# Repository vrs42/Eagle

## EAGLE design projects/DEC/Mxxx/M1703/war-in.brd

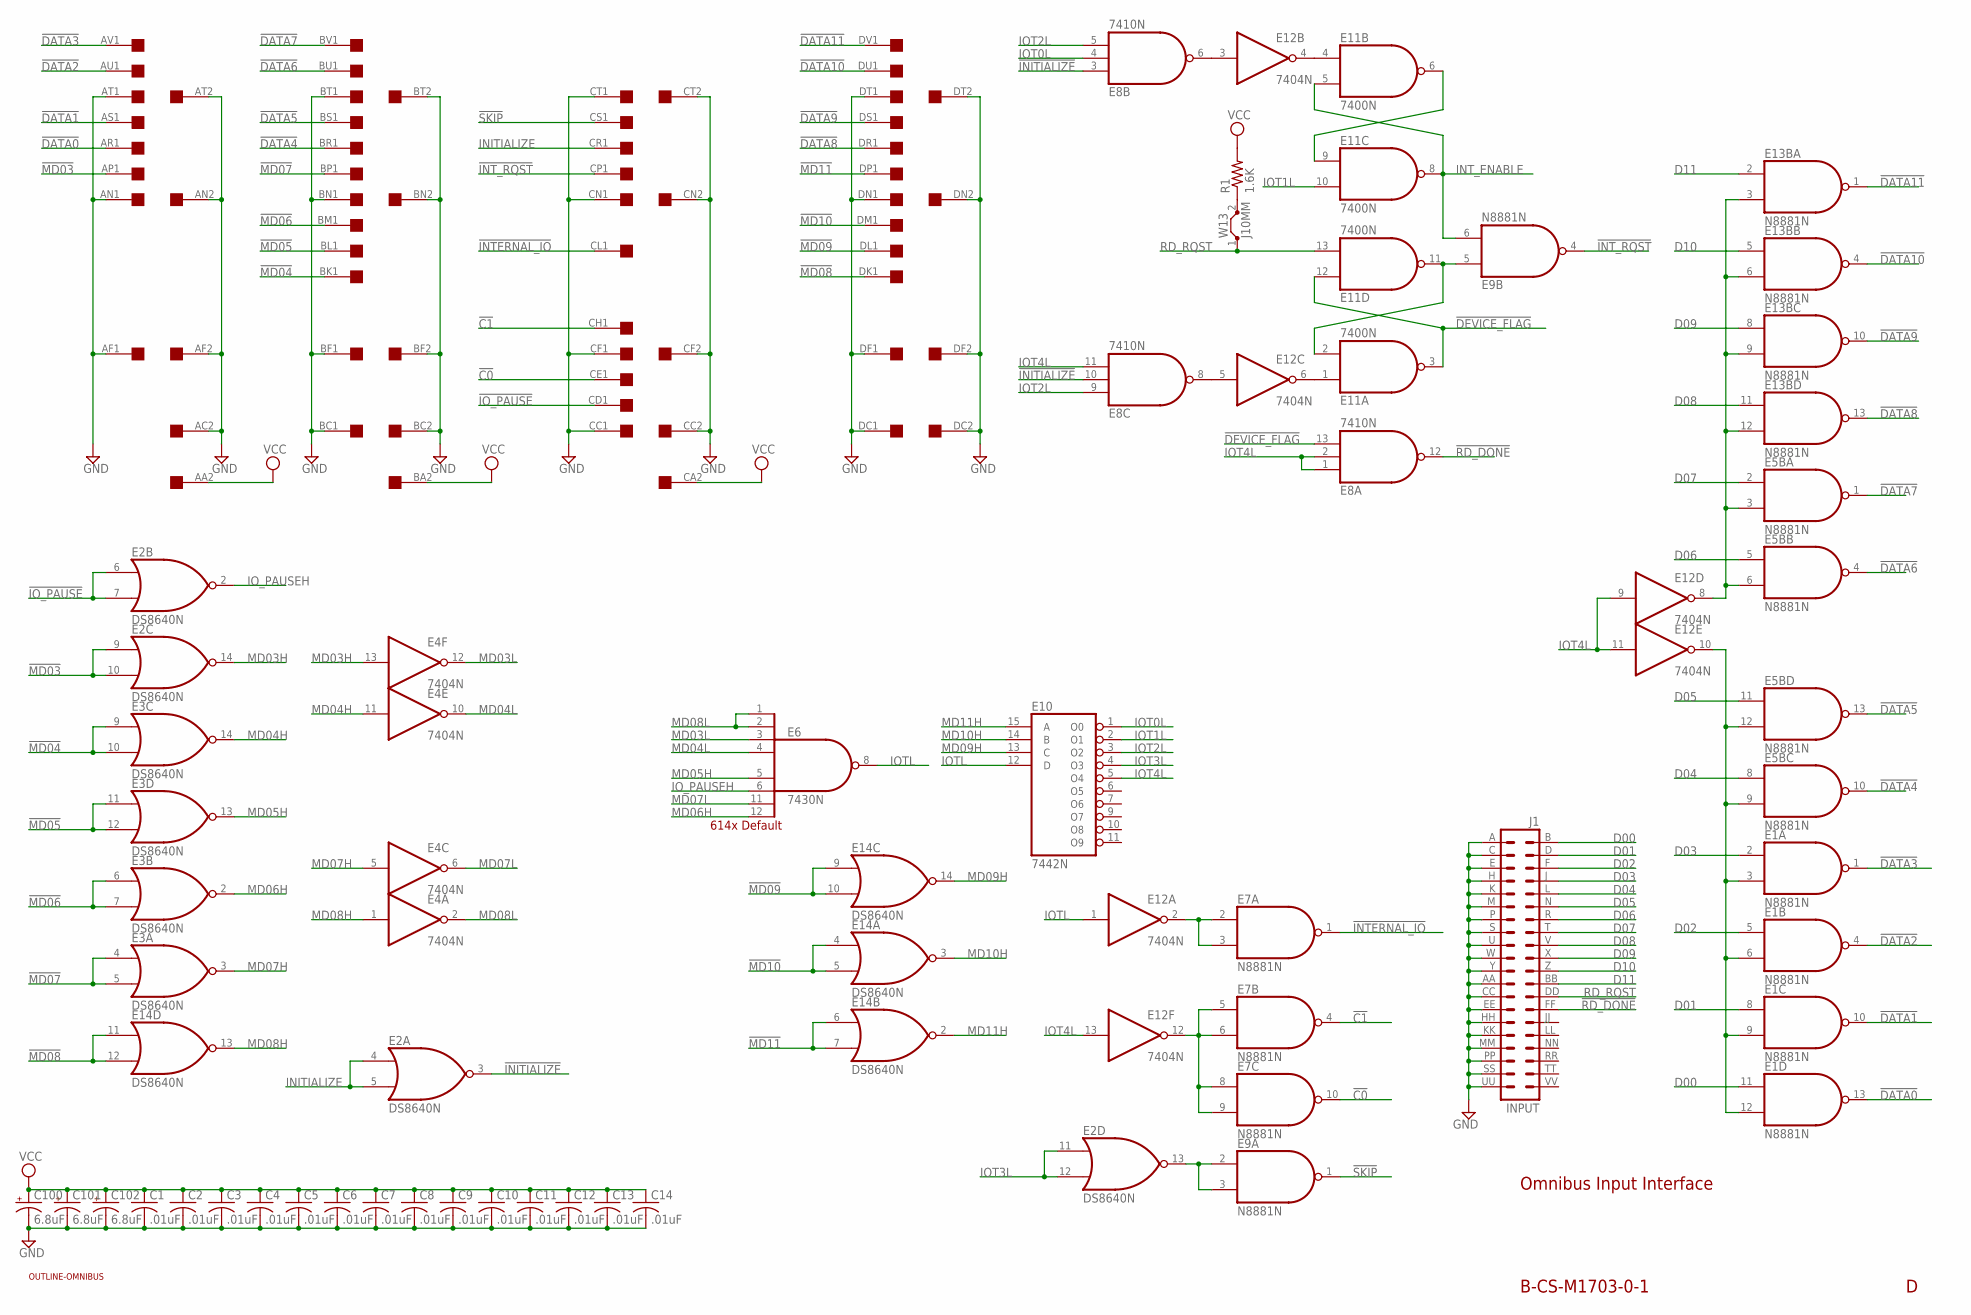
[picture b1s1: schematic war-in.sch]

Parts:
C1, C2, C3, C4, C5, C6, C7, C8, C9, C10, C11, C12, C13, C14: .01uF; C075-032X103
C100, C101, C102: 6.8uF; E12-8
E1, E5B, E7, E9, E13B: N8881N; DIL14
E2, E3, E14: DS8640N; DIL14
E4, E12: 7404N; DIL14
E6: 7430N; DIL14
E8: 7410N; DIL14
E10: 7442N; DIL16
E11: 7400N; DIL14
J1: INPUT; DEC40PINH
R1: 1.6K; 0207/10
U$2: QUAD; EDGE-CON8
U$4: OUTLINE-OMNIBUS; OMNIBUS
W13: J10MM; 10

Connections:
!C0: E7.10 (O), U$2.CE1
!C1: E7.4 (O), U$2.CH1
!DATA0: E1.13 (O), U$2.AR1
!DATA1: E1.10 (O), U$2.AS1
!DATA2: E1.4 (O), U$2.AU1
!DATA3: E1.1 (O), U$2.AV1
!DATA4: E5B.10 (O), U$2.BR1
!DATA5: E5B.13 (O), U$2.BS1
!DATA6: E5B.4 (O), U$2.BU1
!DATA7: E5B.1 (O), U$2.BV1
!DATA8: E13B.13 (O), U$2.DR1
!DATA9: E13B.10 (O), U$2.DS1
!DATA10: E13B.4 (O), U$2.DU1
!DATA11: E13B.1 (O), U$2.DV1
!DEVICE_FLAG: E8.13 (I2), E11.3 (O), E11.12 (I0)
!INITIALIZE: E2.3 (O), E8.3 (I0), E8.10 (I1)
!INTERNAL_IO: E7.1 (O), U$2.CL1
!INT_ENABLE: E11.6 (O), E11.9 (I0)
!INT_RQST: E9.4 (O), U$2.CP1
!IO_PAUSE: E2.6 (I0), E2.7 (I1), U$2.CD1
!MD03: E2.9 (I0), E2.10 (I1), U$2.AP1
!MD04: E3.9 (I0), E3.10 (I1), U$2.BK1
!MD05: E3.11 (I0), E3.12 (I1), U$2.BL1
!MD06: E3.6 (I0), E3.7 (I1), U$2.BM1
!MD07: E3.4 (I0), E3.5 (I1), U$2.BP1
!MD08: E14.11 (I0), E14.12 (I1), U$2.DK1
!MD09: E14.9 (I0), E14.10 (I1), U$2.DL1
!MD10: E14.4 (I0), E14.5 (I1), U$2.DM1
!MD11: E14.6 (I0), E14.7 (I1), U$2.DP1
!RD_DONE: E8.12 (O), J1.FF (28)
!SKIP: E9.1 (O), U$2.CS1
D00: E1.11 (I0), J1.B (2)
D01: E1.8 (I0), J1.D (4)
D02: E1.5 (I0), J1.F (6)
D03: E1.2 (I0), J1.J (8)
D04: E5B.8 (I0), J1.L (10)
D05: E5B.11 (I0), J1.N (12)
D06: E5B.5 (I0), J1.R (14)
D07: E5B.2 (I0), J1.T (16)
D08: E13B.11 (I0), J1.V (18)
D09: E13B.8 (I0), J1.X (20)
D10: E13B.5 (I0), J1.Z (22)
D11: E13B.2 (I0), J1.BB (24)
DEVICE_FLAG: E9.5 (I0), E11.2 (I1), E11.11 (O)
GND: C1.2, C2.2, C3.2, C4.2, C5.2, C6.2, C7.2, C8.2, C9.2, C10.2, C11.2, C12.2, C13.2, C14.2, C100.-, C101.-, C102.-, E1.7 (GND), E2.1 (GND), E3.1 (GND), E4.7 (GND), E5B.7 (GND), E6.7 (GND), E7.7 (GND), E8.7 (GND), E9.7 (GND), E10.8 (GND), E11.7 (GND), E12.7 (GND), E13B.7 (GND), E14.1 (GND), J1.A (1), J1.AA (23), J1.C (3), J1.CC (25), J1.E (5), J1.EE (27), J1.H (7), J1.HH (29), J1.K (9), J1.KK (31), J1.M (11), J1.MM (33), J1.P (13), J1.PP (35), J1.S (15), J1.SS (37), J1.U (17), J1.UU (39), J1.W (19), J1.Y (21), U$2.AC2, U$2.AF1, U$2.AF2, U$2.AN1, U$2.AN2, U$2.AT1, U$2.AT2, U$2.BC1, U$2.BC2, U$2.BF1, U$2.BF2, U$2.BN1, U$2.BN2, U$2.BT1, U$2.BT2, U$2.CC1, U$2.CC2, U$2.CF1, U$2.CF2, U$2.CN1, U$2.CN2, U$2.CT1, U$2.CT2, U$2.DC1, U$2.DC2, U$2.DF1, U$2.DF2, U$2.DN1, U$2.DN2, U$2.DT1, U$2.DT2
INITIALIZE: E2.4 (I0), E2.5 (I1), U$2.CR1
INT_ENABLE: E9.6 (I1), E11.5 (I1), E11.8 (O)
IOT0L: E8.4 (I1), E10.1 (O0)
IOT1L: E10.2 (O1), E11.10 (I1)
IOT2L: E8.5 (I2), E8.9 (I0), E10.3 (O2)
IOT3L: E2.11 (I0), E2.12 (I1), E10.4 (O3)
IOT4L: E8.1 (I0), E8.2 (I1), E8.11 (I2), E10.5 (O4), E12.9 (I), E12.11 (I), E12.13 (I)
IOTL: E6.8 (O), E10.12 (D), E12.1 (I)
IO_PAUSEH: E2.2 (O), E6.6 (I5)
MD03H: E2.14 (O), E4.13 (I)
MD03L: E4.12 (O), E6.3 (I2)
MD04H: E3.14 (O), E4.11 (I)
MD04L: E4.10 (O), E6.4 (I3)
MD05H: E3.13 (O), E6.5 (I4)
MD06H: E3.2 (O), E6.12 (I7)
MD07H: E3.3 (O), E4.5 (I)
MD07L: E4.6 (O), E6.11 (I6)
MD08H: E4.1 (I), E14.13 (O)
MD08L: E4.2 (O), E6.1 (I0), E6.2 (I1)
MD09H: E10.13 (C), E14.14 (O)
MD10H: E10.14 (B), E14.3 (O)
MD11H: E10.15 (A), E14.2 (O)
unnamed: E1.3 (I1), E1.6 (I1), E1.9 (I1), E1.12 (I1), E5B.9 (I1), E5B.12 (I1), E12.10 (O)
unnamed: R1.1, W13.2
unnamed: E5B.3 (I1), E5B.6 (I1), E12.8 (O), E13B.3 (I1), E13B.6 (I1), E13B.9 (I1), E13B.12 (I1)
unnamed: E11.4 (I0), E12.4 (O)
unnamed: E2.13 (O), E9.2 (I0), E9.3 (I1)
unnamed: E8.6 (O), E12.3 (I)
unnamed: E11.1 (I0), E12.6 (O)
unnamed: E8.8 (O), E12.5 (I)
unnamed: E7.2 (I0), E7.3 (I1), E12.2 (O)
unnamed: E7.5 (I0), E7.6 (I1), E7.8 (I0), E7.9 (I1), E12.12 (O)
RD_RQST: E11.13 (I1), J1.DD (26), W13.1
VCC: C1.1, C2.1, C3.1, C4.1, C5.1, C6.1, C7.1, C8.1, C9.1, C10.1, C11.1, C12.1, C13.1, C14.1, C100.+, C101.+, C102.+, E1.14 (VCC), E2.8 (VCC), E3.8 (VCC), E4.14 (VCC), E5B.14 (VCC), E6.14 (VCC), E7.14 (VCC), E8.14 (VCC), E9.14 (VCC), E10.16 (VCC), E11.14 (VCC), E12.14 (VCC), E13B.14 (VCC), E14.8 (VCC), R1.2, U$2.AA2, U$2.BA2, U$2.CA2

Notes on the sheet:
B-CS-M1703-0-1
Omnibus Input Interface
614x Default

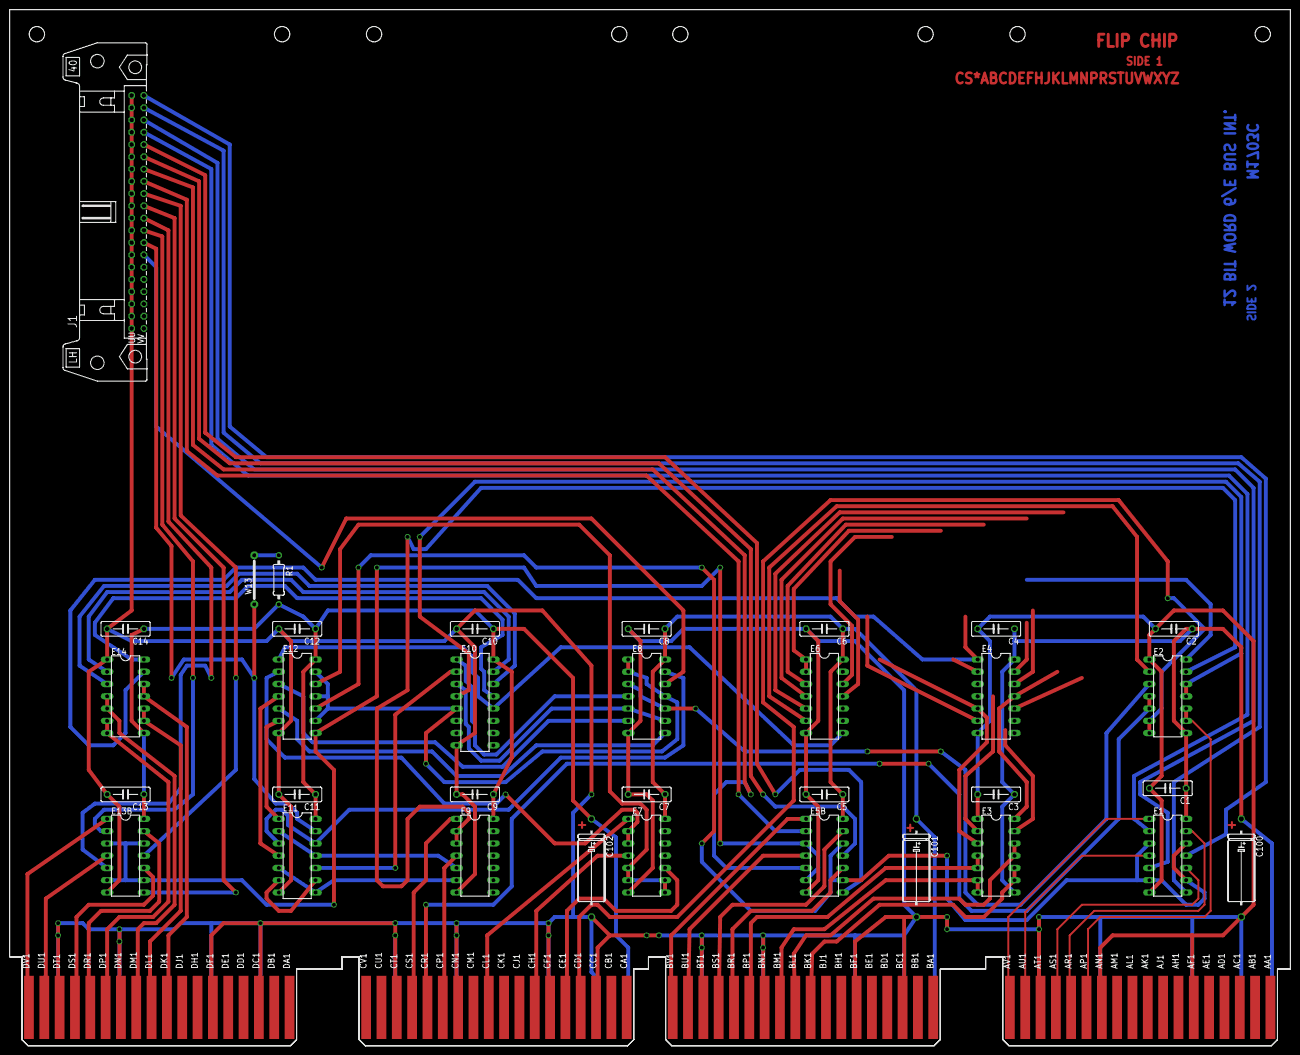
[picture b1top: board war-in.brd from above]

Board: 2 copper layers, 265.3 x 214.6 mm, 37 parts (0 on the bottom side), 79 nets.

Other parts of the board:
U$3: FLIPCHIP

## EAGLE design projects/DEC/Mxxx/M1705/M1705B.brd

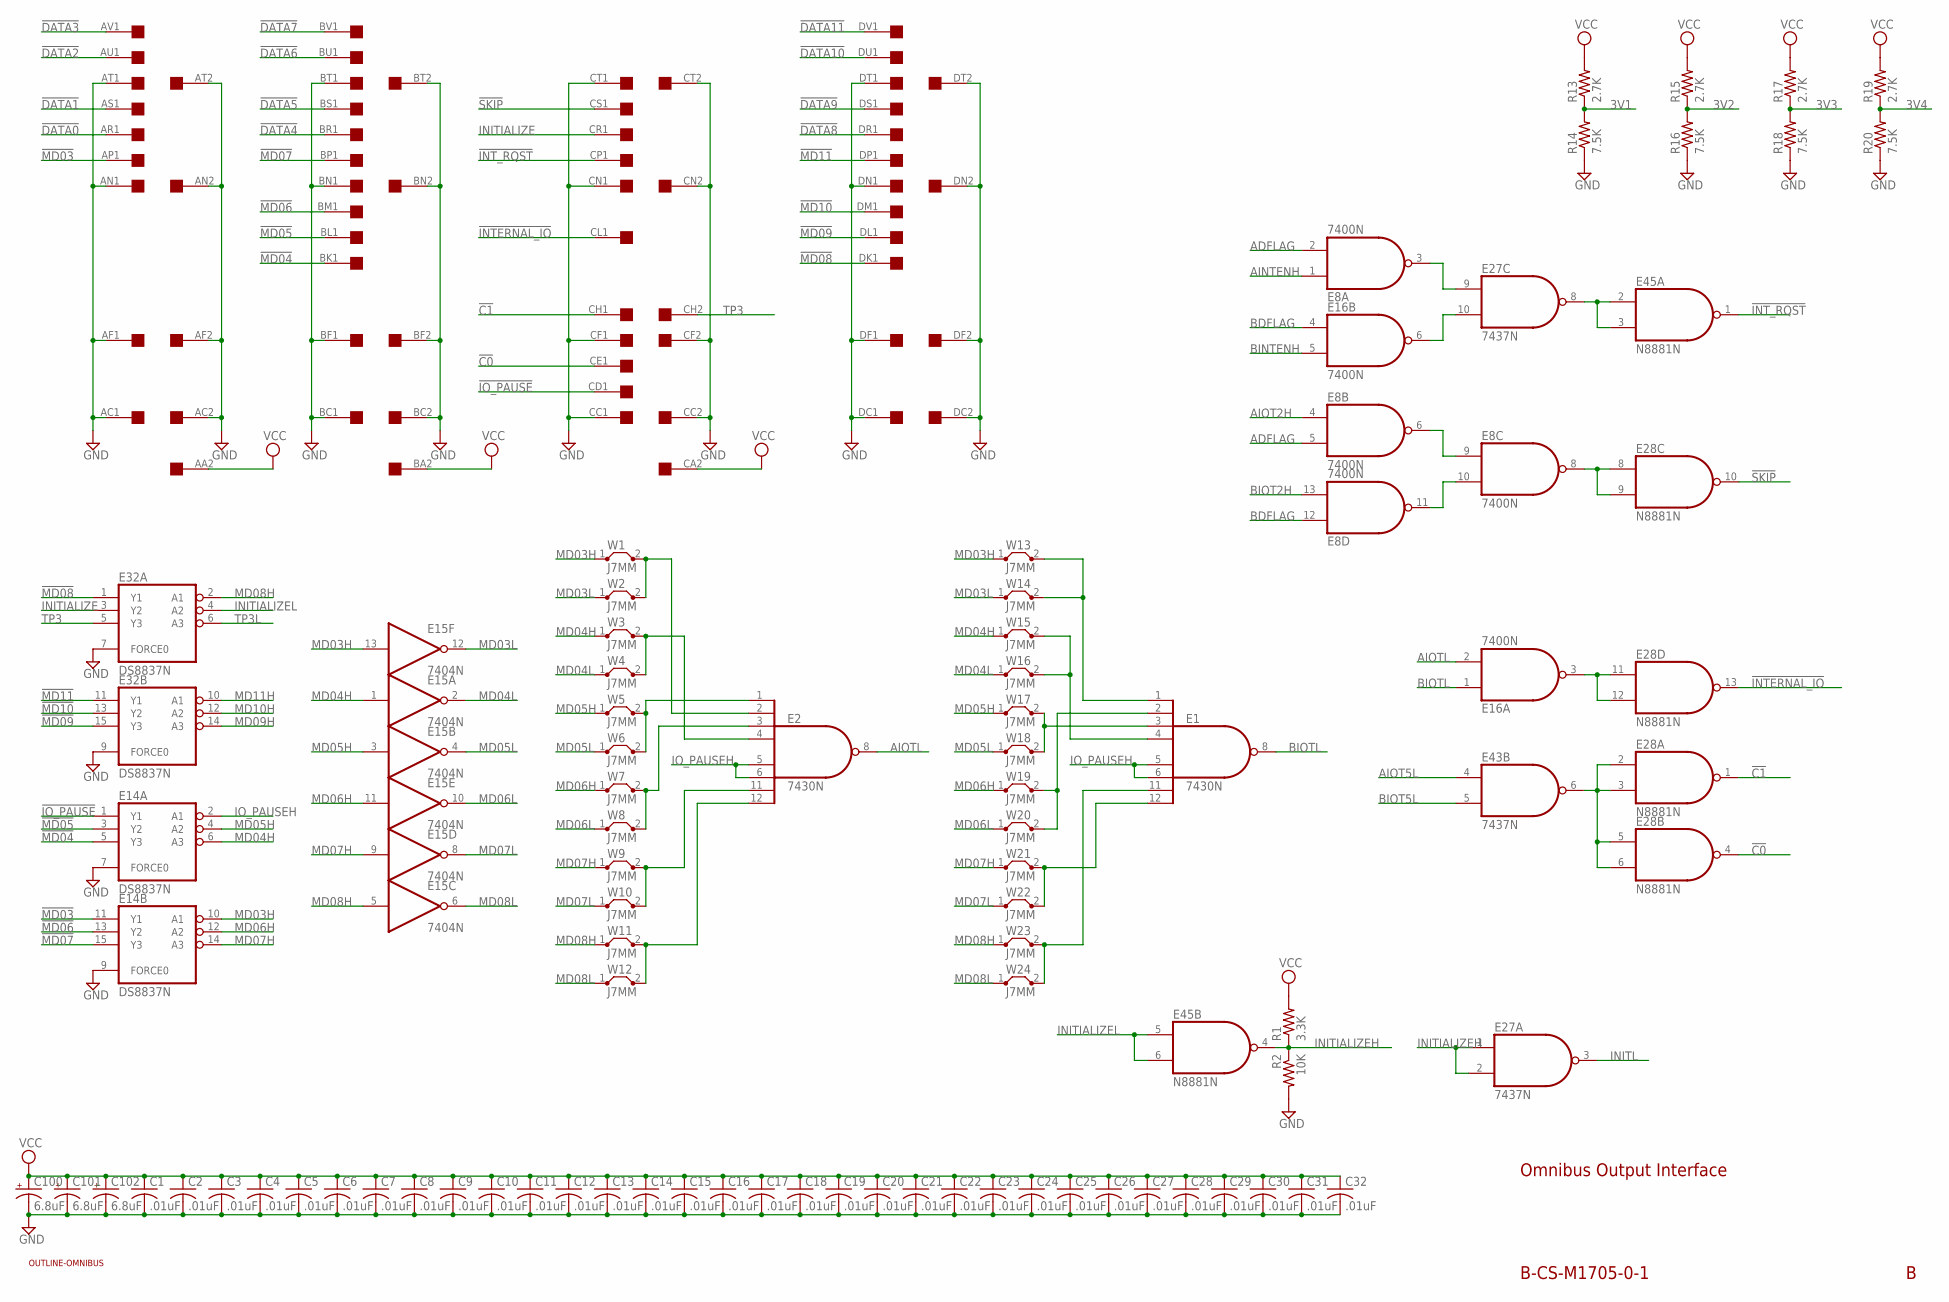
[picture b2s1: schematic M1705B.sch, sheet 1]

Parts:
C1, C2, C3, C4, C5, C6, C7, C8, C9, C10, C11, C12, C13, C14, C15, C16, C17, C18, C19, C20, C21, C22, C23, C24, C25, C26, C27, C28, C29, C30, C31, C32: .01uF; C075-032X103
C100, C101, C102: 6.8uF; E12-8
E1, E2: 7430N; DIL14
E8, E16: 7400N; DIL14
E14, E32: DS8837N; DIL16
E15: 7404N; DIL14
E27, E43: 7437N; DIL14
E28, E45: N8881N; DIL14
R1: 3.3K; 0207/10
R2: 10K; 0207/10
R13, R15, R17, R19: 2.7K; 0207/10
R14, R16, R18, R20: 7.5K; 0207/10
U$2: QUAD; EDGE-CON8
U$4: OUTLINE-OMNIBUS; OMNIBUS
W1, W2, W3, W4, W5, W6, W7, W8, W9, W10, W11, W12, W13, W14, W15, W16, W17, W18, W19, W20, W21, W22, W23, W24: J7MM; 07

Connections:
3V1: R13.1, R14.2; also elsewhere on the board
3V2: R15.1, R16.2; also elsewhere on the board
3V3: R17.1, R18.2; also elsewhere on the board
3V4: R19.1, R20.2; also elsewhere on the board
!C0: E28.4 (O), U$2.CE1
!C1: E28.1 (O), U$2.CH1
!DATA0: U$2.AR1; also elsewhere on the board
!DATA1: U$2.AS1; also elsewhere on the board
!DATA2: U$2.AU1; also elsewhere on the board
!DATA3: U$2.AV1; also elsewhere on the board
!DATA4: U$2.BR1; also elsewhere on the board
!DATA5: U$2.BS1; also elsewhere on the board
!DATA6: U$2.BU1; also elsewhere on the board
!DATA7: U$2.BV1; also elsewhere on the board
!DATA8: U$2.DR1; also elsewhere on the board
!DATA9: U$2.DS1; also elsewhere on the board
!DATA10: U$2.DU1; also elsewhere on the board
!DATA11: U$2.DV1; also elsewhere on the board
!INTERNAL_IO: E28.13 (O), U$2.CL1
!INT_RQST: E45.1 (O), U$2.CP1
!IO_PAUSE: E14.1 (Y1), U$2.CD1
!MD03: E14.11 (Y1), U$2.AP1
!MD04: E14.5 (Y3), U$2.BK1
!MD05: E14.3 (Y2), U$2.BL1
!MD06: E14.13 (Y2), U$2.BM1
!MD07: E14.15 (Y3), U$2.BP1
!MD08: E32.1 (Y1), U$2.DK1
!MD09: E32.15 (Y3), U$2.DL1
!MD10: E32.13 (Y2), U$2.DM1
!MD11: E32.11 (Y1), U$2.DP1
!SKIP: E28.10 (O), U$2.CS1
ADFLAG: E8.2 (I1), E8.5 (I1); also elsewhere on the board
AINTENH: E8.1 (I0); also elsewhere on the board
AIOT2H: E8.4 (I0); also elsewhere on the board
AIOT5L: E43.4 (I0); also elsewhere on the board
AIOTL: E2.8 (O), E16.2 (I1); also elsewhere on the board
BDFLAG: E8.12 (I0), E16.4 (I0); also elsewhere on the board
BINTENH: E16.5 (I1); also elsewhere on the board
BIOT2H: E8.13 (I1); also elsewhere on the board
BIOT5L: E43.5 (I1); also elsewhere on the board
BIOTL: E1.8 (O), E16.1 (I0); also elsewhere on the board
GND: C1.2, C2.2, C3.2, C4.2, C5.2, C6.2, C7.2, C8.2, C9.2, C10.2, C11.2, C12.2, C13.2, C14.2, C15.2, C16.2, C17.2, C18.2, C19.2, C20.2, C21.2, C22.2, C23.2, C24.2, C25.2, C26.2, C27.2, C28.2, C29.2, C30.2, C31.2, C32.2, C100.-, C101.-, C102.-, E1.7 (GND), E2.7 (GND), E8.7 (GND), E14.7 (FORCE0), E14.8 (GND), E14.9 (FORCE0), E15.7 (GND), E16.7 (GND), E27.7 (GND), E28.7 (GND), E32.7 (FORCE0), E32.8 (GND), E32.9 (FORCE0), E43.7 (GND), E45.7 (GND), R2.2, R14.1, R16.1, R18.1, R20.1, U$2.AC1, U$2.AC2, U$2.AF1, U$2.AF2, U$2.AN1, U$2.AN2, U$2.AT1, U$2.AT2, U$2.BC1, U$2.BC2, U$2.BF1, U$2.BF2, U$2.BN1, U$2.BN2, U$2.BT1, U$2.BT2, U$2.CC1, U$2.CC2, U$2.CF1, U$2.CF2, U$2.CN1, U$2.CN2, U$2.CT1, U$2.CT2, U$2.DC1, U$2.DC2, U$2.DF1, U$2.DF2, U$2.DN1, U$2.DN2, U$2.DT1, U$2.DT2; also elsewhere on the board
INITIALIZE: E32.3 (Y2), U$2.CR1
INITIALIZEH: E27.1 (I0), E27.2 (I1), E45.4 (O), R1.1, R2.1
INITIALIZEL: E32.4 (A2), E45.5 (I0), E45.6 (I1); also elsewhere on the board
INITL: E27.3 (O); also elsewhere on the board
IO_PAUSEH: E1.5 (I4), E1.6 (I5), E2.5 (I4), E2.6 (I5), E14.2 (A1)
MD03H: E14.10 (A1), E15.13 (I), W1.1, W13.1
MD03L: E15.12 (O), W2.1, W14.1
MD04H: E14.6 (A3), E15.1 (I), W3.1, W15.1
MD04L: E15.2 (O), W4.1, W16.1
MD05H: E14.4 (A2), E15.3 (I), W5.1, W17.1
MD05L: E15.4 (O), W6.1, W18.1
MD06H: E14.12 (A2), E15.11 (I), W7.1, W19.1
MD06L: E15.10 (O), W8.1, W20.1
MD07H: E14.14 (A3), E15.9 (I), W9.1, W21.1
MD07L: E15.8 (O), W10.1, W22.1
MD08H: E15.5 (I), E32.2 (A1), W11.1, W23.1
MD08L: E15.6 (O), W12.1, W24.1
MD09H: E32.14 (A3); also elsewhere on the board
MD10H: E32.12 (A2); also elsewhere on the board
MD11H: E32.10 (A1); also elsewhere on the board
unnamed: E1.3 (I2), W17.2, W18.2
unnamed: E1.1 (I0), W13.2, W14.2
unnamed: E2.11 (I6), W9.2, W10.2
unnamed: E1.12 (I7), W21.2, W22.2
unnamed: E1.11 (I6), W23.2, W24.2
unnamed: E1.4 (I3), W15.2, W16.2
unnamed: E1.2 (I1), W19.2, W20.2
unnamed: E2.1 (I0), W5.2, W6.2
unnamed: E2.2 (I1), W1.2, W2.2
unnamed: E2.3 (I2), W7.2, W8.2
unnamed: E2.4 (I3), W3.2, W4.2
unnamed: E2.12 (I7), W11.2, W12.2
unnamed: E8.8 (O), E28.8 (I0), E28.9 (I1)
unnamed: E8.3 (O), E27.9 (I0)
unnamed: E8.10 (I1), E8.11 (O)
unnamed: E8.6 (O), E8.9 (I0)
unnamed: E16.3 (O), E28.11 (I0), E28.12 (I1)
unnamed: E16.6 (O), E27.10 (I1)
unnamed: E28.2 (I0), E28.3 (I1), E28.5 (I0), E28.6 (I1), E43.6 (O)
unnamed: E27.8 (O), E45.2 (I0), E45.3 (I1)
TP3: E32.5 (Y3), U$2.CH2
TP3L: E32.6 (A3); also elsewhere on the board
VCC: C1.1, C2.1, C3.1, C4.1, C5.1, C6.1, C7.1, C8.1, C9.1, C10.1, C11.1, C12.1, C13.1, C14.1, C15.1, C16.1, C17.1, C18.1, C19.1, C20.1, C21.1, C22.1, C23.1, C24.1, C25.1, C26.1, C27.1, C28.1, C29.1, C30.1, C31.1, C32.1, C100.+, C101.+, C102.+, E1.14 (VCC), E2.14 (VCC), E8.14 (VCC), E14.16 (VCC), E15.14 (VCC), E16.14 (VCC), E27.14 (VCC), E28.14 (VCC), E32.16 (VCC), E43.14 (VCC), E45.14 (VCC), R1.2, R13.2, R15.2, R17.2, R19.2, U$2.AA2, U$2.BA2, U$2.CA2; also elsewhere on the board

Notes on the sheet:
B-CS-M1705-0-1
Omnibus Output Interface

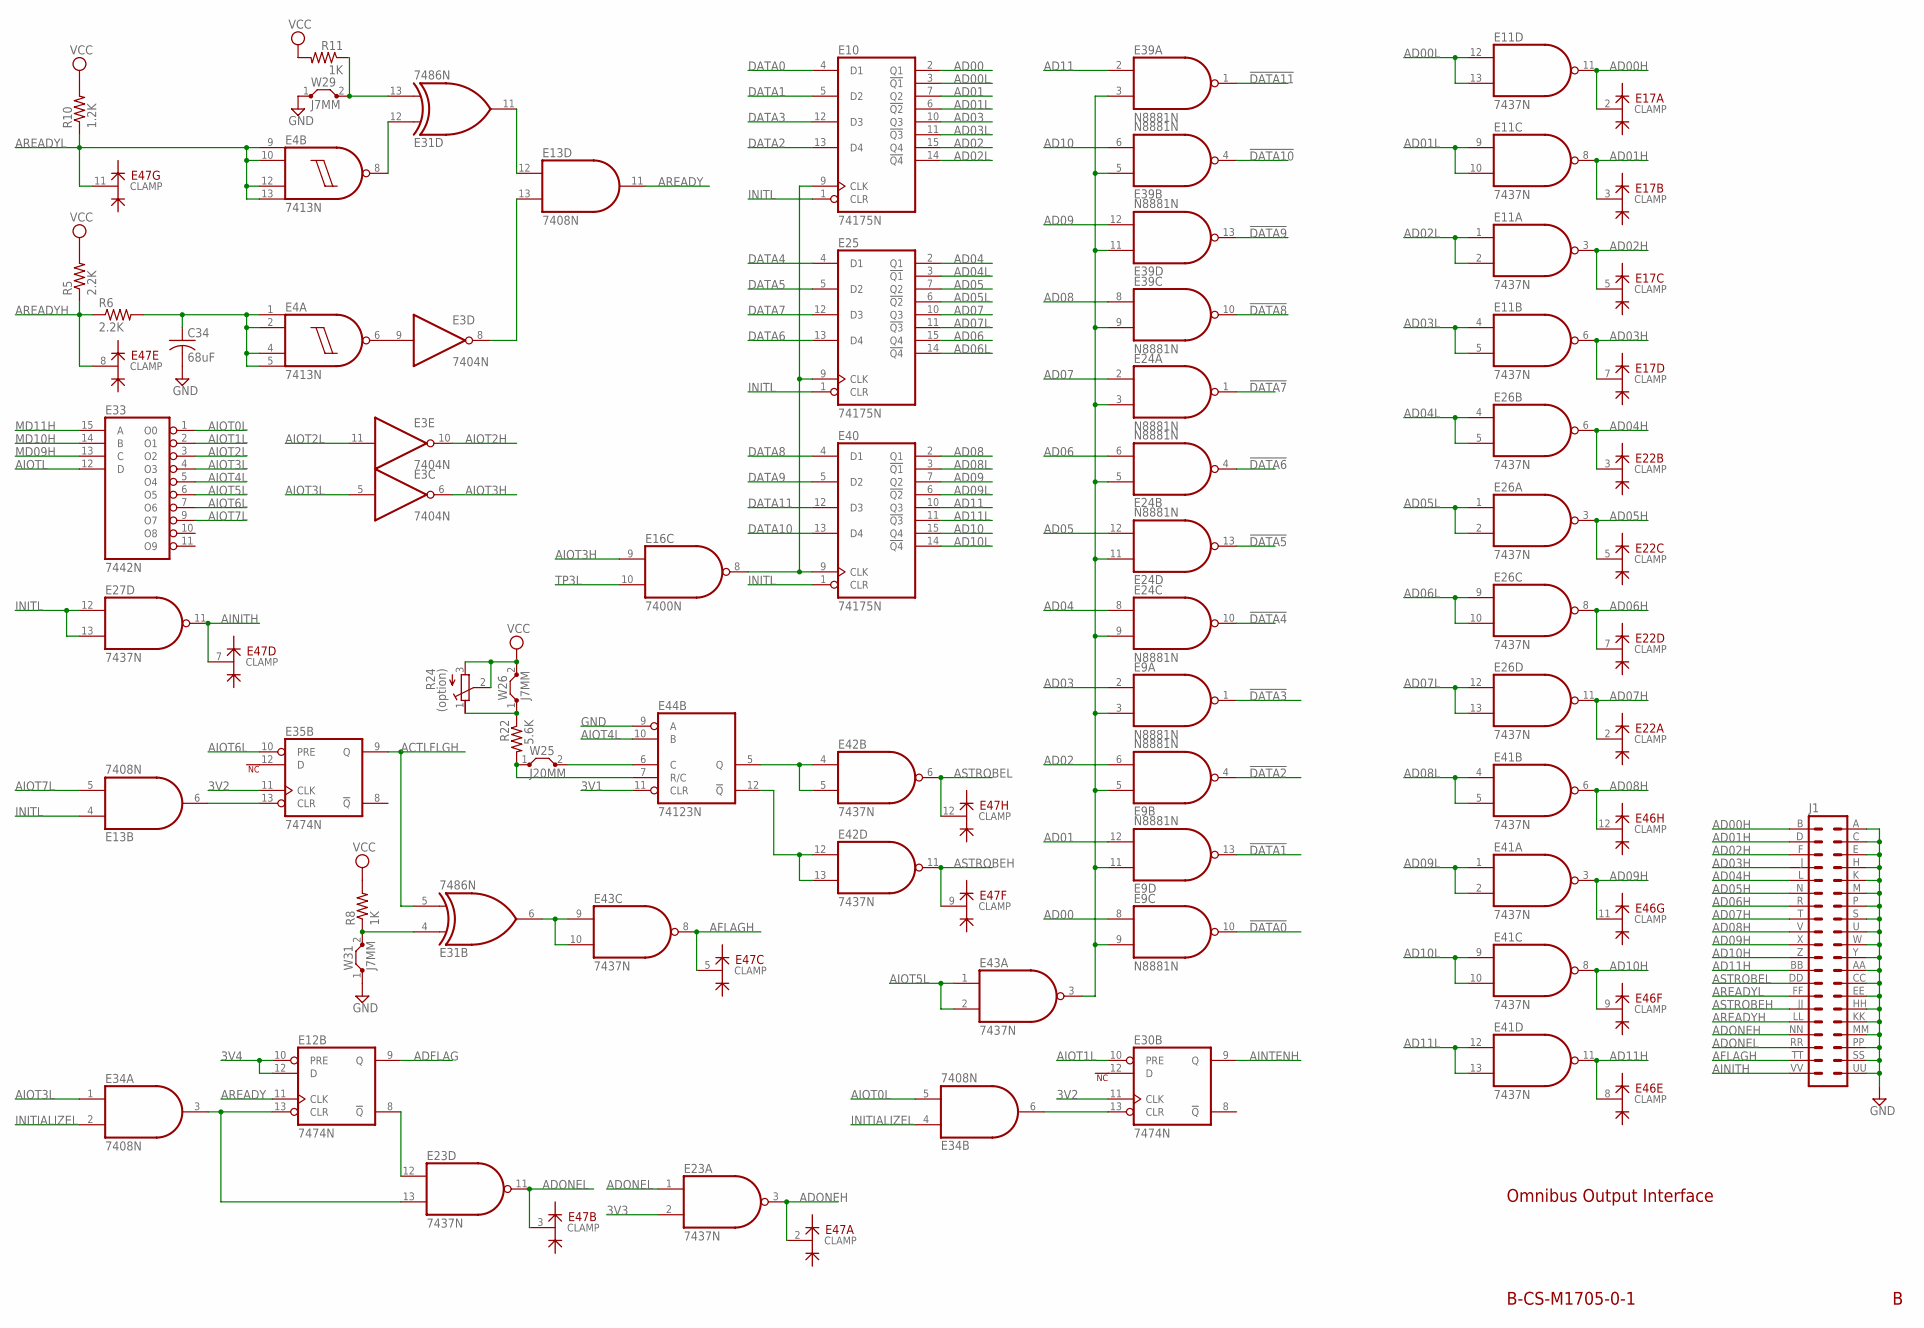
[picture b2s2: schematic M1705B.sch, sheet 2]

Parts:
C34: 68uF; C102-043X133
E3: 7404N; DIL14
E4: 7413N; DIL14
E9, E24, E39: N8881N; DIL14
E10, E25, E40: 74175N; DIL16
E11, E23, E26, E27, E41, E42, E43: 7437N; DIL14
E12, E30, E35: 7474N; DIL14
E13, E34: 7408N; DIL14
E16: 7400N; DIL14
E17, E22, E46, E47: DEC2501; DIL14
E31: 7486N; DIL14
E33: 7442N; DIL16
E44: 74123N; DIL16
J1: DEC40PINH
R5, R6: 2.2K; 0207/10
R8, R11: 1K; 0207/10
R10: 1.2K; 0207/10
R22: 5.6K; 0207/10
R24: (option); 3006Y
W25: J20MM; 20
W26, W29, W31: J7MM; 07

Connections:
3V1: E44.11 (CLR); also elsewhere on the board
3V2: E30.11 (CLK), E35.11 (CLK); also elsewhere on the board
3V3: E23.2 (I1); also elsewhere on the board
3V4: E12.10 (PRE), E12.12 (D); also elsewhere on the board
!DATA0: E9.10 (O); also elsewhere on the board
!DATA1: E9.13 (O); also elsewhere on the board
!DATA2: E9.4 (O); also elsewhere on the board
!DATA3: E9.1 (O); also elsewhere on the board
!DATA4: E24.10 (O); also elsewhere on the board
!DATA5: E24.13 (O); also elsewhere on the board
!DATA6: E24.4 (O); also elsewhere on the board
!DATA7: E24.1 (O); also elsewhere on the board
!DATA8: E39.10 (O); also elsewhere on the board
!DATA9: E39.13 (O); also elsewhere on the board
!DATA10: E39.4 (O); also elsewhere on the board
!DATA11: E39.1 (O); also elsewhere on the board
ACTLFLGH: E31.5 (I1), E35.9 (Q)
AD00: E9.8 (I0), E10.2 (Q1)
AD00H: E11.11 (O), E17.2 (CLAMP), J1.B (2)
AD00L: E10.3 (!Q1), E11.12 (I0), E11.13 (I1)
AD01: E9.12 (I1), E10.7 (Q2)
AD01H: E11.8 (O), E17.3 (CLAMP), J1.D (4)
AD01L: E10.6 (!Q2), E11.9 (I0), E11.10 (I1)
AD02: E9.6 (I1), E10.15 (Q4)
AD02H: E11.3 (O), E17.5 (CLAMP), J1.F (6)
AD02L: E10.14 (!Q4), E11.1 (I0), E11.2 (I1)
AD03: E9.2 (I0), E10.10 (Q3)
AD03H: E11.6 (O), E17.7 (CLAMP), J1.J (8)
AD03L: E10.11 (!Q3), E11.4 (I0), E11.5 (I1)
AD04: E24.8 (I0), E25.2 (Q1)
AD04H: E22.3 (CLAMP), E26.6 (O), J1.L (10)
AD04L: E25.3 (!Q1), E26.4 (I0), E26.5 (I1)
AD05: E24.12 (I1), E25.7 (Q2)
AD05H: E22.5 (CLAMP), E26.3 (O), J1.N (12)
AD05L: E25.6 (!Q2), E26.1 (I0), E26.2 (I1)
AD06: E24.6 (I1), E25.15 (Q4)
AD06H: E22.7 (CLAMP), E26.8 (O), J1.R (14)
AD06L: E25.14 (!Q4), E26.9 (I0), E26.10 (I1)
AD07: E24.2 (I0), E25.10 (Q3)
AD07H: E22.2 (CLAMP), E26.11 (O), J1.T (16)
AD07L: E25.11 (!Q3), E26.12 (I0), E26.13 (I1)
AD08: E39.8 (I0), E40.2 (Q1)
AD08H: E41.6 (O), E46.12 (CLAMP), J1.V (18)
AD08L: E40.3 (!Q1), E41.4 (I0), E41.5 (I1)
AD09: E39.12 (I1), E40.7 (Q2)
AD09H: E41.3 (O), E46.11 (CLAMP), J1.X (20)
AD09L: E40.6 (!Q2), E41.1 (I0), E41.2 (I1)
AD10: E39.6 (I1), E40.15 (Q4)
AD10H: E41.8 (O), E46.9 (CLAMP), J1.Z (22)
AD10L: E40.14 (!Q4), E41.9 (I0), E41.10 (I1)
AD11: E39.2 (I0), E40.10 (Q3)
AD11H: E41.11 (O), E46.8 (CLAMP), J1.BB (24)
AD11L: E40.11 (!Q3), E41.12 (I0), E41.13 (I1)
ADFLAG: E12.9 (Q); also elsewhere on the board
ADONEH: E23.3 (O), E47.2 (CLAMP), J1.NN (34)
ADONEL: E23.1 (I0), E23.11 (O), E47.3 (CLAMP), J1.RR (36)
AFLAGH: E43.8 (O), E47.5 (CLAMP), J1.TT (38)
AINITH: E27.11 (O), E47.7 (CLAMP), J1.VV (40)
AINTENH: E30.9 (Q); also elsewhere on the board
AIOT0L: E33.1 (O0), E34.5 (I1)
AIOT1L: E30.10 (PRE), E33.2 (O1)
AIOT2H: E3.10 (O); also elsewhere on the board
AIOT2L: E3.11 (I), E33.3 (O2)
AIOT3H: E3.6 (O), E16.9 (I0)
AIOT3L: E3.5 (I), E33.4 (O3), E34.1 (I0)
AIOT4L: E33.5 (O4), E44.10 (B)
AIOT5L: E33.6 (O5), E43.1 (I0), E43.2 (I1); also elsewhere on the board
AIOT6L: E33.7 (O6), E35.10 (PRE)
AIOT7L: E13.5 (I1), E33.9 (O7)
AIOTL: E33.12 (D); also elsewhere on the board
AREADY: E12.11 (CLK), E13.11 (O)
AREADYH: E47.8 (CLAMP), J1.LL (32), R5.1, R6.1
AREADYL: E4.9 (I0), E4.10 (I1), E4.12 (I2), E4.13 (I3), E47.11 (CLAMP), J1.FF (28), R10.1
ASTROBEH: E42.11 (O), E47.9 (CLAMP), J1.JJ (30)
ASTROBEL: E42.6 (O), E47.12 (CLAMP), J1.DD (26)
DATA0: E10.4 (D1); also elsewhere on the board
DATA1: E10.5 (D2); also elsewhere on the board
DATA2: E10.13 (D4); also elsewhere on the board
DATA3: E10.12 (D3); also elsewhere on the board
DATA4: E25.4 (D1); also elsewhere on the board
DATA5: E25.5 (D2); also elsewhere on the board
DATA6: E25.13 (D4); also elsewhere on the board
DATA7: E25.12 (D3); also elsewhere on the board
DATA8: E40.4 (D1); also elsewhere on the board
DATA9: E40.5 (D2); also elsewhere on the board
DATA10: E40.13 (D4); also elsewhere on the board
DATA11: E40.12 (D3); also elsewhere on the board
GND: C34.2, E3.7 (GND), E4.7 (GND), E9.7 (GND), E10.8 (GND), E11.7 (GND), E12.7 (GND), E13.7 (GND), E16.7 (GND), E17.14 (GND), E22.14 (GND), E23.7 (GND), E24.7 (GND), E25.8 (GND), E26.7 (GND), E27.7 (GND), E30.7 (GND), E31.7 (GND), E33.8 (GND), E34.7 (GND), E35.7 (GND), E39.7 (GND), E40.8 (GND), E41.7 (GND), E42.7 (GND), E43.7 (GND), E44.8 (GND), E44.9 (A), E46.14 (GND), E47.14 (GND), J1.A (1), J1.AA (23), J1.C (3), J1.CC (25), J1.E (5), J1.EE (27), J1.H (7), J1.HH (29), J1.K (9), J1.KK (31), J1.M (11), J1.MM (33), J1.P (13), J1.PP (35), J1.S (15), J1.SS (37), J1.U (17), J1.UU (39), J1.W (19), J1.Y (21), W29.1, W31.1; also elsewhere on the board
INITIALIZEL: E34.2 (I1), E34.4 (I0); also elsewhere on the board
INITL: E10.1 (CLR), E13.4 (I0), E25.1 (CLR), E27.12 (I0), E27.13 (I1), E40.1 (CLR); also elsewhere on the board
MD09H: E33.13 (C); also elsewhere on the board
MD10H: E33.14 (B); also elsewhere on the board
MD11H: E33.15 (A); also elsewhere on the board
unnamed: E9.3 (I1), E9.5 (I0), E9.9 (I1), E9.11 (I0), E24.3 (I1), E24.5 (I0), E24.9 (I1), E24.11 (I0), E39.3 (I1), E39.5 (I0), E39.9 (I1), E39.11 (I0), E43.3 (O)
unnamed: E10.9 (CLK), E16.8 (O), E25.9 (CLK), E40.9 (CLK)
unnamed: E3.9 (I), E4.6 (O)
unnamed: E3.8 (O), E13.13 (I1)
unnamed: C34.1, E4.1 (I0), E4.2 (I1), E4.4 (I2), E4.5 (I3), R6.2
unnamed: E4.8 (O), E31.12 (I0)
unnamed: E31.13 (I1), R11.1, W29.2
unnamed: E12.13 (CLR), E23.13 (I1), E34.3 (O)
unnamed: E12.8 (!Q), E23.12 (I0)
unnamed: E31.4 (I0), R8.1, W31.2
unnamed: E13.6 (O), E35.13 (CLR)
unnamed: E13.12 (I0), E31.11 (O)
unnamed: E30.13 (CLR), E34.6 (O)
unnamed: E31.6 (O), E43.9 (I0), E43.10 (I1)
unnamed: E44.6 (C), W25.2
unnamed: E44.7 (R/C), R22.2, W25.1
unnamed: R22.1, R24.1 (A), W26.1
unnamed: E42.12 (I0), E42.13 (I1), E44.12 (!Q)
unnamed: E42.4 (I0), E42.5 (I1), E44.5 (Q)
TP3L: E16.10 (I1); also elsewhere on the board
VCC: E3.14 (VCC), E4.14 (VCC), E9.14 (VCC), E10.16 (VCC), E11.14 (VCC), E12.14 (VCC), E13.14 (VCC), E16.14 (VCC), E17.1 (VCC), E22.1 (VCC), E23.14 (VCC), E24.14 (VCC), E25.16 (VCC), E26.14 (VCC), E27.14 (VCC), E30.14 (VCC), E31.14 (VCC), E33.16 (VCC), E34.14 (VCC), E35.14 (VCC), E39.14 (VCC), E40.16 (VCC), E41.14 (VCC), E42.14 (VCC), E43.14 (VCC), E44.16 (VCC), E46.1 (VCC), E47.1 (VCC), R5.2, R8.2, R10.2, R11.2, R24.2 (S), R24.3 (E), W26.2; also elsewhere on the board

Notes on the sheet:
B-CS-M1705-0-1
Omnibus Output Interface
